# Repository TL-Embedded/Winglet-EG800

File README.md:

# Winglet-EG800

An implementation of the [winglet](https://github.com/TL-Embedded/Winglet-Carrier/blob/main/winglet-modem.md) form factor using the EG800Q modem.

The EEPROM id string shall read: `EG800Q`.

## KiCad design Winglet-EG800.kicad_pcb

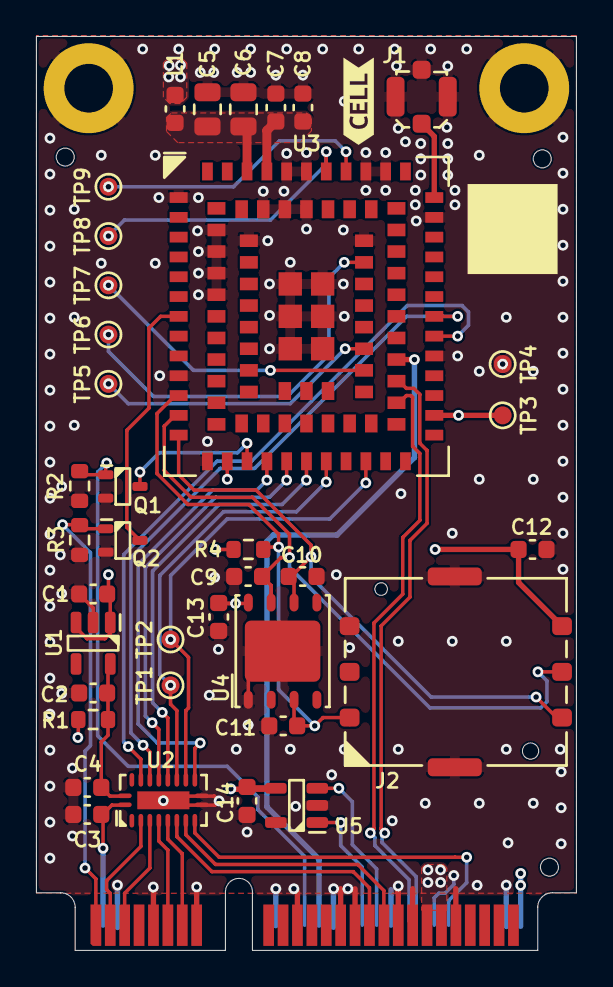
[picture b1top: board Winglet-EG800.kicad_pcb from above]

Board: 4 copper layers, 30.0 x 50.8 mm, 45 parts (0 on the bottom side), 39 nets.

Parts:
C1, C2, C3, C4, C7, C12, C13, C14: 100n; C_0603
C5, C6: 47u,6.3V; C_0805
C8, C9, C10, C11: 33p; C_0603
J1: 2337019-1; U.FL
J2: NSIM-16-B
L1: MH1608-601Y; FB_0603
MP1, MP2: PTH_M2.5
N1: QR 5mm; QR_5mm_JLC
N2, N3, N4: ToolingHole; ToolingHole_1mm
N5: PCIe-Mini
Q1, Q2: DMG1012UW-7; SC70-3
R1: 0R; R_0603
R2, R3, R4: 10K; R_0603
TP1, TP2, TP3, TP4, TP5, TP6, TP7, TP8, TP9: TestPoint_1mm
U1: MCP1711T-18I/OT; SOT23_5
U2: FXLA108BQX; WQFN20_05_4.5x2.5
U3: EG800QEULC-N03-SNNSA; EG800Q
U4: MFF2-SIM; DFN8_127_5x6_EP
U5: 24AA01T-I/OT; SOT23_5
kibuzzard-66AE0588: G***; kibuzzard-66AE0588

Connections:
+1V8: C2.1, C4.1, R1.1, U1.5 (VOUT), U2.20 (VCCB)
+1V8_MODEM: R1.2, TP3.1 (1_1), U3.24 (VDD_EXT)
+BATT: C1.1, L1.2, N5.39, N5.41, N5.52, U1.1 (VIN), U1.3 (~SHDN)
+VDDIO: C3.1, C14.1, N5.2, U2.1 (VCCA), U5.4 (VCC)
/Connector/AUX_RX: N5.3, U2.3 (A1)
/Connector/AUX_TX: N5.5, U2.4 (A2)
/Connector/DCD: N5.33, U2.8 (A6)
/Connector/DTR: N5.31, U2.7 (A5)
/Connector/I2C_SCL: N5.30, U5.1 (SCL)
/Connector/I2C_SDA: N5.32, U5.3 (SDA)
/Connector/MODEM_AUX_RX: U2.18 (B1), U3.28 (AUX_RXD)
/Connector/MODEM_AUX_TX: U2.17 (B2), U3.29 (AUX_TXD)
/Connector/MODEM_DCD: TP2.1 (1_1), U2.13 (B6), U3.21 (MAIN_DCD)
/Connector/MODEM_DTR: TP1.1 (1_1), U2.14 (B5), U3.19 (MAIN_DTR)
/Connector/MODEM_NETLIGHT: U2.12 (B7), U3.16 (NET_STATUS)
/Connector/MODEM_PWRKEY: Q2.3 (D), U3.7 (~PWRKEY)
/Connector/MODEM_RESET: Q1.3 (D), U3.15 (~RESET)
/Connector/MODEM_RX: U2.16 (B3), U3.17 (MAIN_RXD)
/Connector/MODEM_TX: U2.15 (B4), U3.18 (MAIN_TXD)
/Connector/NETLIGHT: N5.42, U2.9 (A7)
/Connector/RESET: N5.22, Q1.1 (G), R2.1
/Connector/RX: N5.11, U2.5 (A3)
/Connector/TX: N5.13, U2.6 (A4)
/Connector/USB_DM: N5.36, U3.59 (USB_DP)
/Connector/USB_DP: N5.38, U3.60 (USB_DM)
/Connector/USB_VBUS: N5.24, U3.61 (USB_VBUS)
/Connector/WAKE: N5.1, Q2.1 (G), R3.1
/Memory/USIM_CLK: C10.1, J2.C3 (CLK), U3.13 (USIM_CLK), U4.6 (CLK)
/Memory/USIM_DATA: C11.1, J2.C7 (I/O), R4.2, U3.11 (USIM_DATA), U4.3 (I/O)
/Memory/USIM_RST: C9.1, J2.C2 (~RST), U3.12 (USIM_RST), U4.7 (~RST)
/Memory/USIM_VDD: C12.1, C13.1, J2.C1 (VCC), R4.1, U3.14 (USIM_VDD), U4.8 (VCC)
/Modem/VBAT: C5.1, C6.1, C7.1, C8.1, L1.1, U3.42 (VBAT), U3.43 (VBAT)
GND: C1.2, C2.2, C3.2, C4.2, C5.2, C6.2, C7.2, C8.2, C9.2, C10.2, C11.2, C12.2, C13.2, C14.2, J1.S (SHIELD), J2.C5 (GND), J2.S (SHIELD), MP1.1, MP2.1, N5.4, N5.9, N5.15, N5.18, N5.21, N5.26, N5.27, N5.29, N5.34, N5.35, N5.37, N5.40, N5.43, N5.50, Q1.2 (S), Q2.2 (S), R2.2, R3.2, TP4.1 (1_1), U1.2 (GND), U2.10 (GND), U2.11 (~OE), U2.21 (EP), U3.1 (GND), U3.10 (GND), U3.27 (GND), U3.34 (GND), U3.36 (GND), U3.37 (GND), U3.40 (GND), U3.41 (GND), U3.45 (GND), U3.46 (GND), U3.47 (GND), U3.48 (GND), U3.70 (GND), U3.71 (GND), U3.72 (GND), U3.73 (GND), U3.88 (GND), U3.89 (GND), U3.90 (GND), U3.91 (GND), U3.92 (GND), U3.93 (GND), U3.94 (GND), U3.95 (GND), U4.1 (GND), U4.9 (EP), U5.2 (GND), U5.5 (WP)
unnamed: J1.1 (SIGNAL), U3.35 (ANT_MAIN)
unnamed: TP9.1 (1_1), U3.38 (DBG_RXD)
unnamed: TP8.1 (1_1), U3.39 (DBG_TXD)
unnamed: TP5.1 (1_1), U3.83 (PSM_IND)
unnamed: TP6.1 (1_1), U3.87 (PSM_INT)
unnamed: TP7.1 (1_1), U3.82 (~USB_BOOT)

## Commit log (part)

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2026-03-03 Add test points. Finish layout
2026-03-04 Update release format
